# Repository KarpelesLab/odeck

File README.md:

# odeck

An open-hardware USB-C deck you can order fully assembled from JLCPCB and use as a bare PCB the day it
arrives: USB-C upstream, display out, USB-A, SD + microSD, 2.5 GbE, up to **140 W** pass-through
charging, a small status LCD instead of a wall of LEDs, and an RP2350 you can reprogram.

The long-term goal is a **40 Gbps USB4** deck. The first board, **odeck-10**, is a 10 Gbps USB-C deck
built only from parts JLC stocks, to prove out everything the USB4 version will reuse: power, PD,
firmware, display, card reader, Ethernet, board shape and silkscreen.

> **Status (2026-10): schematic complete and reviewed, placement done (DRC-clean, unrouted) — not routed,
> not fabricated.** Placement is code: `hardware/odeck-10/layout/*.py` (one script per board region, see
> `docs/floorplan.md`). The LCD panel and the two JAE USB-C receptacles have no 3D model yet, and the
> GPIO header is shown although it ships unpopulated. More views: [top](docs/images/odeck-10-top.png) ·
> [bottom](docs/images/odeck-10-bottom.png).

## odeck-10 at a glance

| | |
|---|---|
| Upstream | USB-C, USB 3.2 Gen 2 (10 Gbps) + DisplayPort Alt Mode (2-lane HBR3, 4K60) |
| Charging the laptop | USB PD 3.1 EPR up to **140 W** (28 V × 5 A), 100 W SPR fallback |
| Power inputs | USB-C PD in (EPR, up to 48 V) · DC barrel 5.5×2.5 mm 9–24 V · or bus-powered from the laptop |
| Display | Downstream USB-C with DP Alt Mode (works with any USB-C→HDMI/DP cable) |
| USB | 2× USB-A 10 Gbps (BC1.2 charging), downstream USB-C 10 Gbps, forced-5 V "dumb charge" mode with auto-off |
| Storage | SD + microSD (Genesys GL3224) |
| Network | 2.5 GbE (Realtek RTL8156BG) |
| Brains | RP2350B — drives a 2.0" 320×240 IPS status LCD, reads every PD contract / link speed / temperature / port current, and updates every other chip's firmware from a single UF2 |
| Hackable | 2 user buttons, unpopulated GPIO header (series-R + ESD protected), Qwiic connector, SWD |
| Board | 6-layer JLC impedance stack-up (JLC061611-1080A), 130×89 mm, ~800 parts (double-sided), all JLC stock |

### Architecture

```
 Laptop USB-C ══ TUSB1064 ══ USB 10G ══► Microchip USB7206C hub ──► USB-A ×2 · GL3224 (SD/µSD) · RTL8156BG (2.5GbE)
 (10G + DP alt,      ║                                        └──► downstream USB-C ◄══ TUSB1046 ◄═ DP 2-lane
  140 W EPR out)     ╚═════════════ DP lanes + AUX ═══════════════════════════════╝      (USB2 port → RP2350)

 Infineon PMG1-S3: laptop port (EPR source, DP UFP_D) + downstream port (5 V/3 A, DP DFP_D)
 TI TPS26750: USB-C PD-in sink (up to 48 V)        Barrel 9–24 V ─┐
 PD-in ─► ideal-diode OR ◄──────────────────────────────────────────┘ → VIN 9–48 V
   VIN ─► LM51770 buck-boost → 5–28 V × 5 A → laptop (gated, interlocked, hardware OVP)
   VIN ─► LM5148 → 5 V / 8 A → 3.3 V, 1.15 V …     laptop VBUS ─► 5 V when bus-powered
 RP2350B: LCD, buttons, I²C to PD controllers / INA2xx power monitors / 8× TMP1075 / hub SMBus
```

## Repository layout

| Path | What |
|---|---|
| `docs/requirements.md` | Goals and constraints for the whole project (USB4 end goal) |
| `docs/odeck-10.md` | **Start here** — odeck-10 architecture, part choices, design rules, integration items, status |
| `docs/power-budget.md`, `docs/board-layout.md` | Power/thermal budget, outline & placement plan, stack-up |
| `docs/design/*.md` | Per-sheet design notes with every calculation |
| `docs/review/*.md` | Independent schematic and footprint reviews, with resolutions |
| `docs/research/*.md` | Chip, JLC capability and sourcing research (incl. why 40G is not buildable from JLC stock yet) |
| `hardware/odeck-10/` | KiCad 10 project. Schematic sheets are **generated** from `sheets/*.py` |
| `hardware/lib/` | Project symbols, footprints (all checked against manufacturer drawings) and 3D models |
| `tools/schgen/` | Schematics-as-code generator + netlist verification |
| `tools/pcbsync.py` | Scripted "update PCB from schematic" (keeps placed parts where they are; `--refresh` reloads footprints) |
| `tools/apply_layout.py`, `tools/apply_routing.py` | Placement-as-code and routing-as-code runners (`layout/*.py`, `routing/*.py`) |
| `tools/autoroute.py` | Freerouting wrapper for the non-critical nets |
| `tools/bom_check.py` | Checks every part against live JLC stock (rule: JLC parts only, ≥ 5 in stock) |
| `tools/import_lcsc.sh` | Imports LCSC parts (symbol/footprint/3D) via easyeda2kicad |

## Working on it

Requires KiCad 10 (`/Applications/KiCad` on macOS) and Python 3.10+.

```sh
# regenerate every schematic sheet from its Python source and verify the netlist
python3 hardware/odeck-10/sheets/build_all.py

# electrical rules check
/Applications/KiCad/KiCad.app/Contents/MacOS/kicad-cli sch erc hardware/odeck-10/odeck-10.kicad_sch

# every part in JLC stock?  (+ cost summary)
python3 tools/bom_check.py

# push schematic changes into the PCB (uses KiCad's bundled Python)
/Applications/KiCad/KiCad.app/Contents/Frameworks/Python.framework/Versions/3.9/bin/python3 tools/pcbsync.py hardware/odeck-10

# render
/Applications/KiCad/KiCad.app/Contents/MacOS/kicad-cli pcb render --side top -o top.png hardware/odeck-10/odeck-10.kicad_pcb
```

Edit schematics by editing `hardware/odeck-10/sheets/<sheet>.py`, never the generated `.kicad_sch`.
Inter-sheet nets are declared in `tools/schgen/nets.py`.

## Roadmap

1. **odeck-10** (10 Gbps, JLC parts only) — schematic ✅ · review ✅ · footprints ✅ · placement ✅ ·
   routing ⏳ · firmware · order prototypes · bring-up
2. **20/40 Gbps USB4** — waiting on a USB4 hub controller (and its firmware) that can actually be sourced;
   see `docs/research/usb4-hub.md`.

## License

- **Hardware** — everything under `hardware/` (schematics, sheet sources, PCB, symbols, footprints, 3D
  models we created) and the hardware documentation in `docs/`: **CERN-OHL-P v2**
  ([LICENSE-HARDWARE](LICENSE-HARDWARE)).
  Copyright © 2026 Karpelès Lab Inc.
- **Software** — `tools/` and future firmware: **MIT** ([LICENSE-SOFTWARE](LICENSE-SOFTWARE)).

Not covered: third-party datasheets in `docs/datasheets/` (copyright of their manufacturers, included for
reference), footprints/3D models derived from KiCad's libraries or LCSC/EasyEDA (their own terms), and vendor
firmware/libraries (e.g. Infineon's PD stack), which are fetched at build time and never committed.

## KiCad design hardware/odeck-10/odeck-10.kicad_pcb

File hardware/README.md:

# Hardware

KiCad 10 projects.

- `odeck-10/` — 10 Gbps prototype (see `../docs/odeck-10.md`, `../docs/board-layout.md`)
  - Hierarchical schematic: one sheet per block (power input, laptop power out, rails, PD controller,
    USB-C muxes & DP, USB hub, USB-A, Ethernet, card reader, MCU, display & UI, sensors)
  - PCB: JLC061611-1080A 6-layer stackup, 110 × 75 mm provisional outline, JLC design rules, net classes
- `lib/` — shared project symbol/footprint libraries (`odeck.kicad_sym`, `odeck.pretty`), referenced via
  each project's `sym-lib-table` / `fp-lib-table`. Parts from LCSC can be imported with `easyeda2kicad`.

CLI checks:

```sh
K=/Applications/KiCad/KiCad.app/Contents/MacOS/kicad-cli
$K sch erc odeck-10/odeck-10.kicad_sch
$K pcb drc odeck-10/odeck-10.kicad_pcb
```

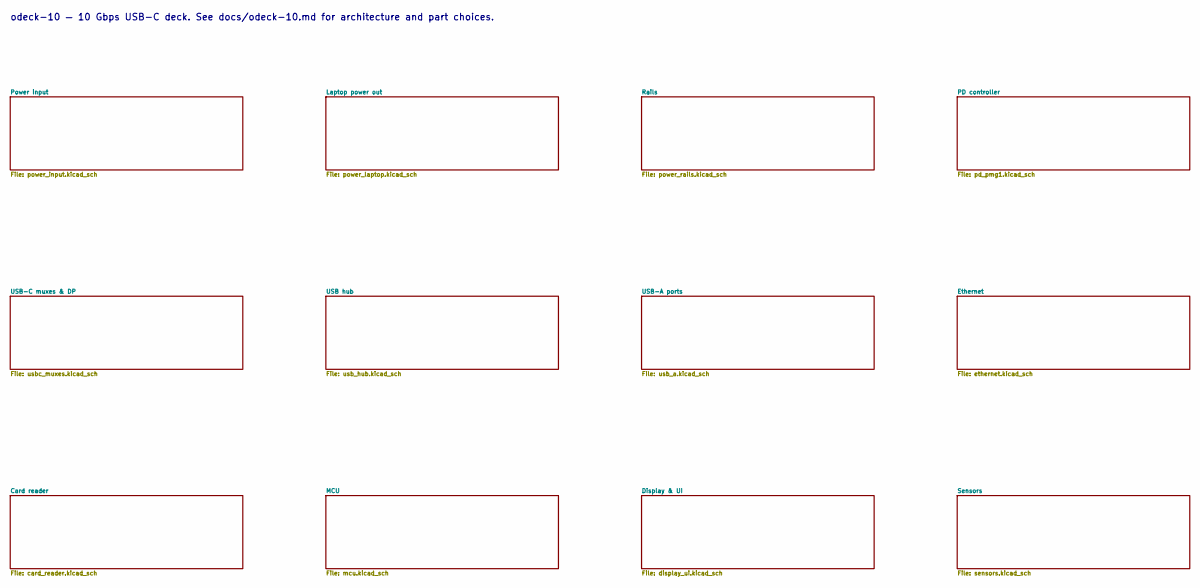
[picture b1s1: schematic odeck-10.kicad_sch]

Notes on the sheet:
odeck-10 — 10 Gbps USB-C deck. See docs/odeck-10.md for architecture and part choices.

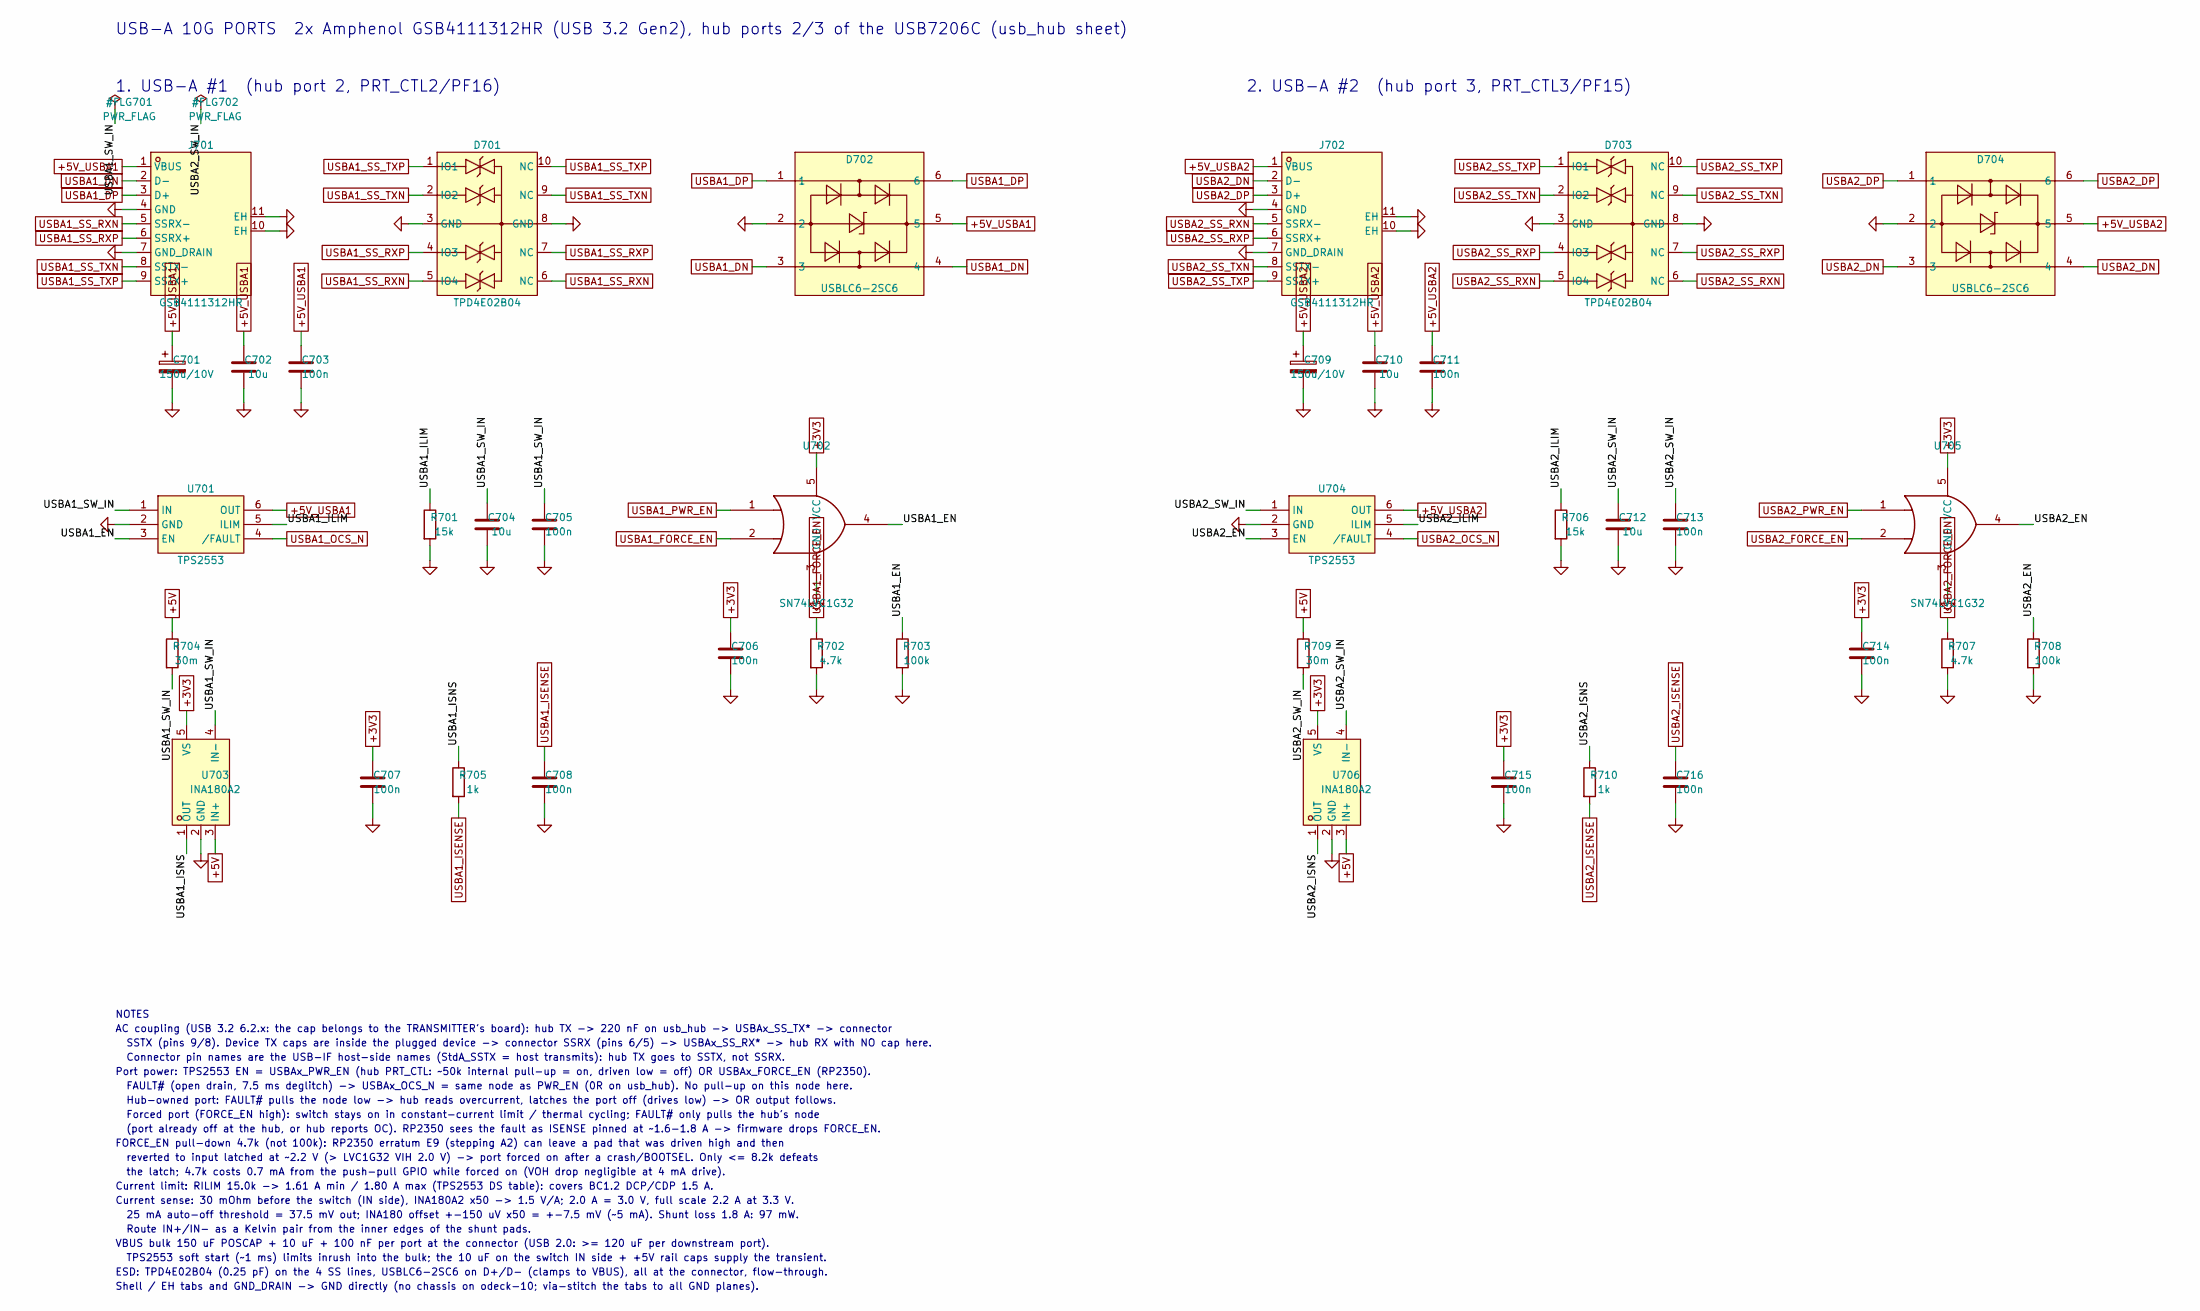
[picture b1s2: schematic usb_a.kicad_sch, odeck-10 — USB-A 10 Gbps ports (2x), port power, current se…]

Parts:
C701, C709: 150u/10V; CP_EIA-7343-31_Kemet-D; LCSC C347559
C702, C704, C710, C712: 10u; C_0805_2012Metric; LCSC C15850
C703, C705, C706, C707, C708, C711, C713, C714, C715, C716: 100n; C_0402_1005Metric; LCSC C1525
D701, D703: TPD4E02B04; USON-10_L2.5-W1.0-P0.50-BL; MPN TPD4E02B04DQAR; LCSC C106794
D702, D704: USBLC6-2SC6; SOT-23-6_L2.9-W1.6-P0.95-LS2.8-BL; MPN USBLC6-2SC6; LCSC C7519
J701, J702: GSB4111312HR; USB-A_Amphenol_GSB4111312HR; MPN GSB4111312HR; LCSC C5429382
R701, R706: 15k; R_0402_1005Metric; LCSC C25756
R702, R707: 4.7k; R_0402_1005Metric; LCSC C25900
R703, R708: 100k; R_0402_1005Metric; LCSC C25741
R704, R709: 30m; R_0805_2012Metric; LCSC C858599
R705, R710: 1k; R_0402_1005Metric; LCSC C11702
U701, U704: TPS2553; SOT-23-6_L2.9-W1.6-P0.95-LS2.8-BR; MPN TPS2553DBVR; LCSC C55266
U702, U705: SN74LVC1G32; SOT-23-5; LCSC C10096
U703, U706: INA180A2; SOT-23-5_L3.0-W1.7-P0.95-LS2.8-BL; MPN INA180A2IDBVR; LCSC C192764

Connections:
+3V3: C706.1, C707.1, C714.1, C715.1, U702.5 (VCC), U703.5 (VS), U705.5 (VCC), U706.5 (VS); also elsewhere on the board
+5V: R704.1, R709.1, U703.3 (IN+), U706.3 (IN+); also elsewhere on the board
+5V_USBA1: C701.1, C702.1, C703.1, D702.5, J701.1 (VBUS), U701.6 (OUT)
+5V_USBA2: C709.1, C710.1, C711.1, D704.5, J702.1 (VBUS), U704.6 (OUT)
/USB-A ports/USBA1_EN: R703.1, U701.3 (EN), U702.4
/USB-A ports/USBA1_ILIM: R701.1, U701.5 (ILIM)
/USB-A ports/USBA1_ISNS: R705.1, U703.1 (OUT)
/USB-A ports/USBA1_SW_IN: C704.1, C705.1, R704.2, U701.1 (IN), U703.4 (IN-)
/USB-A ports/USBA2_EN: R708.1, U704.3 (EN), U705.4
/USB-A ports/USBA2_ILIM: R706.1, U704.5 (ILIM)
/USB-A ports/USBA2_ISNS: R710.1, U706.1 (OUT)
/USB-A ports/USBA2_SW_IN: C712.1, C713.1, R709.2, U704.1 (IN), U706.4 (IN-)
GND: C701.2, C702.2, C703.2, C704.2, C705.2, C706.2, C707.2, C708.2, C709.2, C710.2, C711.2, C712.2, C713.2, C714.2, C715.2, C716.2, D701.3 (GND), D701.8 (GND), D702.2, D703.3 (GND), D703.8 (GND), D704.2, J701.4 (GND), J701.7 (GND_DRAIN), J701.10 (EH), J701.11 (EH), J702.4 (GND), J702.7 (GND_DRAIN), J702.10 (EH), J702.11 (EH), R701.2, R702.2, R703.2, R706.2, R707.2, R708.2, U701.2 (GND), U702.3 (GND), U703.2 (GND), U704.2 (GND), U705.3 (GND), U706.2 (GND); also elsewhere on the board
USBA1_DN: D702.3, D702.4, J701.2 (D-); also elsewhere on the board
USBA1_DP: D702.1, D702.6, J701.3 (D+); also elsewhere on the board
USBA1_FORCE_EN: R702.1, U702.2; also elsewhere on the board
USBA1_ISENSE: C708.1, R705.2; also elsewhere on the board
USBA1_OCS_N: U701.4 (/FAULT); also elsewhere on the board
USBA1_PWR_EN: U702.1; also elsewhere on the board
USBA1_SS_RXN: D701.5 (IO4), D701.6 (NC), J701.5 (SSRX-); also elsewhere on the board
USBA1_SS_RXP: D701.4 (IO3), D701.7 (NC), J701.6 (SSRX+); also elsewhere on the board
USBA1_SS_TXN: D701.2 (IO2), D701.9 (NC), J701.8 (SSTX-); also elsewhere on the board
USBA1_SS_TXP: D701.1 (IO1), D701.10 (NC), J701.9 (SSTX+); also elsewhere on the board
USBA2_DN: D704.3, D704.4, J702.2 (D-); also elsewhere on the board
USBA2_DP: D704.1, D704.6, J702.3 (D+); also elsewhere on the board
USBA2_FORCE_EN: R707.1, U705.2; also elsewhere on the board
USBA2_ISENSE: C716.1, R710.2; also elsewhere on the board
USBA2_OCS_N: U704.4 (/FAULT); also elsewhere on the board
USBA2_PWR_EN: U705.1; also elsewhere on the board
USBA2_SS_RXN: D703.5 (IO4), D703.6 (NC), J702.5 (SSRX-); also elsewhere on the board
USBA2_SS_RXP: D703.4 (IO3), D703.7 (NC), J702.6 (SSRX+); also elsewhere on the board
USBA2_SS_TXN: D703.2 (IO2), D703.9 (NC), J702.8 (SSTX-); also elsewhere on the board
USBA2_SS_TXP: D703.1 (IO1), D703.10 (NC), J702.9 (SSTX+); also elsewhere on the board

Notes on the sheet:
USB-A 10G PORTS 2x Amphenol GSB4111312HR (USB 3.2 Gen2), hub ports 2/3 of the USB7206C (usb_hub sheet)
1. USB-A #1 (hub port 2, PRT_CTL2/PF16)
2. USB-A #2 (hub port 3, PRT_CTL3/PF15)
NOTES
AC coupling (USB 3.2 6.2.x: the cap belongs to the TRANSMITTER's board): hub TX -> 220 nF on usb_hub -> USBAx_SS_TX* -> connector
SSTX (pins 9/8). Device TX caps are inside the plugged device -> connector SSRX (pins 6/5) -> USBAx_SS_RX* -> hub RX with NO cap here.
Connector pin names are the USB-IF host-side names (StdA_SSTX = host transmits): hub TX goes to SSTX, not SSRX.
Port power: TPS2553 EN = USBAx_PWR_EN (hub PRT_CTL: ~50k internal pull-up = on, driven low = off) OR USBAx_FORCE_EN (RP2350).
FAULT# (open drain, 7.5 ms deglitch) -> USBAx_OCS_N = same node as PWR_EN (0R on usb_hub). No pull-up on this node here.
Hub-owned port: FAULT# pulls the node low -> hub reads overcurrent, latches the port off (drives low) -> OR output follows.
Forced port (FORCE_EN high): switch stays on in constant-current limit / thermal cycling; FAULT# only pulls the hub's node
(port already off at the hub, or hub reports OC). RP2350 sees the fault as ISENSE pinned at ~1.6-1.8 A -> firmware drops FORCE_EN.
FORCE_EN pull-down 4.7k (not 100k): RP2350 erratum E9 (stepping A2) can leave a pad that was driven high and then
reverted to input latched at ~2.2 V (> LVC1G32 VIH 2.0 V) -> port forced on after a crash/BOOTSEL. Only <= 8.2k defeats
the latch; 4.7k costs 0.7 mA from the push-pull GPIO while forced on (VOH drop negligible at 4 mA drive).
Current limit: RILIM 15.0k -> 1.61 A min / 1.80 A max (TPS2553 DS table): covers BC1.2 DCP/CDP 1.5 A.
Current sense: 30 mOhm before the switch (IN side), INA180A2 x50 -> 1.5 V/A; 2.0 A = 3.0 V, full scale 2.2 A at 3.3 V.
25 mA auto-off threshold = 37.5 mV out; INA180 offset +-150 uV x50 = +-7.5 mV (~5 mA). Shunt loss 1.8 A: 97 mW.
Route IN+/IN- as a Kelvin pair from the inner edges of the shunt pads.
VBUS bulk 150 uF POSCAP + 10 uF + 100 nF per port at the connector (USB 2.0: >= 120 uF per downstream port).
TPS2553 soft start (~1 ms) limits inrush into the bulk; the 10 uF on the switch IN side + +5V rail caps supply the transient.
ESD: TPD4E02B04 (0.25 pF) on the 4 SS lines, USBLC6-2SC6 on D+/D- (clamps to VBUS), all at the connector, flow-through.
Shell / EH tabs and GND_DRAIN -> GND directly (no chassis on odeck-10; via-stitch the tabs to all GND planes).

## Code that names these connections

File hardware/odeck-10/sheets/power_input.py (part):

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           "EPR_BLK_G unused (no 5 V source FET: sink-only port). SBU channels unused.",
           at=(20.32, 12.7))
    s.part("odeck:DX07S024XJ1R1100", "J", "USB-C PD-in", at=(45.72, 76.2),
           pins={"VBUS": "VBUS_PDIN", "CC1": "PDIN_C_CC1", "CC2": "PDIN_C_CC2", "GND": "GND", "0": "GND"},
           nc=["A2", "A3", "B2", "B3", "A10", "A11", "B10", "B11", "A6", "A7", "B6", "B7", "A8", "B8"],
           desc="USB-C receptacle 24P, 5 A / 48 V, PD-in (power only)")
    s.part("odeck:SMCJ51A_C408371", "D", TVS_PDIN[1], at=(91.44, 60.96), pins={"C": "VBUS_PDIN", "A": "GND"},
           lcsc=TVS_PDIN[0], mpn=TVS_PDIN[1], desc="TVS 51 V uni 5 kW (SMC), VBUS_PDIN")
    s.c("2.2u/100V", "VBUS_PDIN", "GND", size="1210", at=(83.82, 81.28), lcsc=C_2U2_100V)
    s.c("100n/100V", "VBUS_PDIN", "GND", size="0805", at=(93.98, 81.28), lcsc=C_100N_100V)
    s.flag("VBUS_PDIN", at=(104.14, 81.28))

    s.part("odeck:TPD4S480RUKR_C43131250", "U", "TPD4S480", at=(152.4, 76.2),
           pins={"VBUS": "VBUS_PDIN", "VBUS_LV": "PDIN_VBUS_LV", "EPR_EN": "PDIN_EPR_EN", "VPWR": "PD_LDO_3V3",
                 "VBIAS": "PDIN_VBIAS", "C_CC1": "PDIN_C_CC1", "RPD_G1": "PDIN_C_CC1", "C_CC2": "PDIN_C_CC2",
                 "RPD_G2": "PDIN_C_CC2", "CC1": "PDIN_CC1", "CC2": "PDIN_CC2", "~{FLT}": "PDIN_FLT_N",
                 "GND": "GND", "EP": "GND"},
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           "  (SafeMode alternative: ADCIN1 -> LDO_3V3, ADCIN2 -> GND = 7/0, address 0x20.)\n"
           "Config/patch from AT24C512C (64 KB >= 36 KB req.) at 0x50 on the private I2Cc bus.\n"
           "  RP2350 updates it through the TPS26750 host interface (I2Ct, 0x21); I2Cc test pads for recovery.\n"
           "GPIO0 = EPR_EN (to TPD4S480), GPIO1 = PDIN_PRESENT (informational only, 47k series: <= 60 uA into an\n"
           "  unpowered PMG1/RP2350 pin; config: high while sink contract active),\n"
           "GPIO2 = TPD4S480 FLT# input, other GPIOs strapped to GND through 100k (datasheet: tie low if unused).\n"
           "PP5V tied to GND: sink-only port, no 5 V sourcing / VCONN (verify with TI).\n"
           "I2C_PD pull-ups live on the MCU sheet; PDIN_INT_N pull-up here.",
           at=(205.74, 12.7))
    s.part("odeck:TPS26750SRSMR_C42166327", "U", "TPS26750", at=(271.78, 83.82),
           pins={"VIN_3V3": "+3V3", "LDO_3V3": "PD_LDO_3V3", "LDO_1V5": "PD_LDO_1V5",
                 "VBUS": "PDIN_VBUS_LV", "PP5V": "GND", "CC1": "PDIN_CC1", "CC2": "PDIN_CC2",
                 "ADCIN1": "PD_ADCIN1", "ADCIN2": "PD_ADCIN2",
                 "GPIO0": "PDIN_EPR_EN", "GPIO1": "PDIN_PRES_L", "GPIO2": "PDIN_FLT_N",
                 "GPIO3": "PD_GPIO3", "GPIO4/USB_P/LD1": "PD_GPIO4", "GPIO5/USB_N/LD2": "PD_GPIO5",
                 "GPIO6": "PD_GPIO6", "GPIO7": "PD_GPIO7", "GPIO11": "PD_GPIO11",
                 "I2Ct_SDA": "I2C_PD_SDA", "I2Ct_SCL": "I2C_PD_SCL", "~{I2Ct_IRQ}": "PDIN_INT_N",
                 "I2Cc_SDA": "PD_I2CC_SDA", "I2Cc_SCL": "PD_I2CC_SCL", "~{I2Cc_IRQ}": "PD_I2CC_IRQ_N",
                 "POWER_PATH_EN": "PD_PP_EN_HV", "GND": "GND"},
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    s.r("4.7k", "PD_I2CC_SCL", "PD_LDO_3V3", at=(x0 + 121.92, y0), lcsc=R_4K7)   # during dead-battery EEPROM boot
    # unused GPIOs -> GND through 100k (Hi-Z by default; resistor protects if a config drives them)
    y1 = 180.34
    for i, g in enumerate(["PD_GPIO3", "PD_GPIO4", "PD_GPIO5", "PD_GPIO6", "PD_GPIO7", "PD_GPIO11"]):
        s.r("100k", g, "GND", at=(x0 + i * 10.16, y1), lcsc=R_100K)
    # PDIN_PRESENT: GPIO1, default low. 47k series: GPIO1 can be high (VBUS-LDO powered) while PMG1 P7.2 (not
    # fail-safe) and the RP2350 are unpowered -> (3.3 - 0.5) V / 47k = 60 uA < 0.5 mA PMG1 injection limit.
    s.r("100k", "PDIN_PRES_L", "GND", at=(x0 + 60.96, y1), lcsc=R_100K)
    s.r("47k", "PDIN_PRES_L", "PDIN_PRESENT", at=(x0 + 71.12, y1), lcsc=R_47K)
    s.r("100k", "PDIN_EPR_EN", "GND", at=(x0 + 81.28, y1), lcsc=R_100K)

    s.part("odeck:AT24C512C-SSHD-T", "U", "AT24C512C", at=(355.6, 76.2),
           pins={"A0": "GND", "A1": "GND", "A2": "GND", "WP": "GND", "VCC": "PD_LDO_3V3", "GND": "GND",
                 "SDA": "PD_I2CC_SDA", "SCL": "PD_I2CC_SCL"},
           desc="512 Kbit I2C EEPROM, TPS26750 config/patch (0x50)")
    s.c("100n", "PD_LDO_3V3", "GND", at=(345.44, 96.52), lcsc=C_100N_16V)
    s.part("Connector:TestPoint", "TP", "I2Cc_SDA", "TestPoint:TestPoint_Pad_D1.0mm", at=(360.68, 96.52),
           pins={"1": "PD_I2CC_SDA"})
    s.part("Connector:TestPoint", "TP", "I2Cc_SCL", "TestPoint:TestPoint_Pad_D1.0mm", at=(370.84, 96.52),
           pins={"1": "PD_I2CC_SCL"})

    # POWER_PATH_EN buffer (datasheet Fig. 8-5): POWER_PATH_EN is a 6-12 V / 10 uA charge-pump output,
    # buffered by two NFETs into a logic-level PD_SINK_EN (LDO_3V3 domain).
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           "Q103: pulls PD_OK low while the sink path is off.", at=(480.06, 154.94))
    xb, yb = 495.3, 180.34
    s.part("Transistor_FET:2N7002", "Q", "2N7002", at=(xb, yb), lcsc="C8545",
           pins={"G": "PD_PP_EN_HV", "D": "PD_PP_EN_INV", "S": "GND"})
    s.part("Transistor_FET:2N7002", "Q", "2N7002", at=(xb + 22.86, yb), lcsc="C8545",
           pins={"G": "PD_PP_EN_INV", "D": "PD_SINK_EN", "S": "GND"})
    s.part("Transistor_FET:2N7002", "Q", "2N7002", at=(xb + 45.72, yb), lcsc="C8545",
           pins={"G": "PD_PP_EN_INV", "D": "PD_OK", "S": "GND"})
    s.r("100k", "PD_PP_EN_INV", "PD_LDO_3V3", at=(xb, yb + 25.4), lcsc=R_100K)
    s.r("100k", "PD_SINK_EN", "PD_LDO_3V3", at=(xb + 22.86, yb + 25.4), lcsc=R_100K)

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           "Reverse/backfeed from VIN (barrel or buck-boost) blocked by Q104 (ideal diode).\n"
           "Conduction: 5 A x 2 x 2.6 mOhm = 0.13 W.",
           at=(406.4, 12.7))
    s.part(FET, "Q", "BSC026N08NS5", at=(429.26, 63.5), pins={"S": "VBUS_PDIN", "D": "PD_MID", "G": "PD_DGATE"},
           desc="80 V NFET, PD-in ideal diode")
    s.part(FET, "Q", "BSC026N08NS5", at=(487.68, 63.5), pins={"S": "VIN_OR", "D": "PD_MID", "G": "PD_HGATE"},
           desc="80 V NFET, PD-in load switch")
    s.part("odeck:LM74800QDRRRQ1", "U", "LM74800-Q1", at=(457.2, 101.6),
           pins={"DGATE": "PD_DGATE", "A": "VBUS_PDIN", "VSNS": "VBUS_PDIN", "SW": "PD_OV_TOP", "OV": "PD_OV",
                 "EN/UVLO": "PD_SINK_EN", "GND": "GND", "HGATE": "PD_HGATE", "OUT": "VIN_OR", "VS": "PD_MID",
                 "CAP": "PD_CAP", "C": "PD_MID"},
           nc=["RTN"], desc="Ideal diode + load switch controller, PD-in")
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           "Inrush: HGATE 55 uA into 47 nF -> 1.17 V/ms. Conduction: 8.3 A x 2 x 2.6 mOhm = 0.36 W.",
           at=(20.32, 198.12))
    s.part("odeck:PJ-063BH_C3095900", "J", "PJ-063BH", at=(30.48, 254.0),
           pins={"1": "VBAR", "2": "GND"}, nc=["0"], desc="DC jack 5.5x2.5 mm, 8 A")
    s.part("odeck:SMCJ48CA_C408370", "D", TVS_BAR[1], at=(63.5, 246.38), pins={"1": "VBAR", "2": "GND"},
           lcsc=TVS_BAR[0], mpn=TVS_BAR[1], desc="TVS 48 V bidirectional 5 kW (SMC), barrel")
    s.c("100n/100V", "VBAR", "GND", size="0805", at=(78.74, 261.62), lcsc=C_100N_100V)
    s.part(FET, "Q", "BSC026N08NS5", at=(116.84, 246.38), pins={"S": "VBAR", "D": "BAR_MID", "G": "BAR_DGATE"},
           desc="80 V NFET, barrel ideal diode")
    s.part(FET, "Q", "BSC026N08NS5", at=(175.26, 246.38), pins={"S": "VIN_OR", "D": "BAR_MID", "G": "BAR_HGATE"},
           desc="80 V NFET, barrel OV/UVLO/enable switch")
    s.part("odeck:LM74800QDRRRQ1", "U", "LM74800-Q1", at=(147.32, 284.48),
           pins={"DGATE": "BAR_DGATE", "A": "VBAR", "VSNS": "VBAR", "SW": "BAR_SW", "OV": "BAR_OV",
                 "EN/UVLO": "BAR_EN", "GND": "GND", "HGATE": "BAR_HGATE", "OUT": "VIN_OR", "VS": "BAR_MID",
                 "CAP": "BAR_CAP", "C": "BAR_MID"},
           nc=["RTN"], desc="Ideal diode + load switch controller, barrel (RTN pad floating per datasheet)")
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           "PD_OK: TLV6700 window on VBUS_PDIN, 1M/47k/7.5k: UV 7.7 V, OV 56.2 V, AND sink path on (Q103).\n"
           "  A 5 V-only PD contract therefore does NOT count as external power.\n"
           "The laptop sink switch is released only when EXT_PWR_PRESENT AND PG_5V (power_laptop), so a\n"
           "  slightly early EXT_PWR_PRESENT (VIN still ramping) never browns out the deck.\n"
           "Open-drain outputs wired-AND per source, pull-ups to +3V3; 74LVC1G32 OR -> EXT_PWR_PRESENT.\n"
           "All of it runs from +3V3, which exists whenever anything powers the deck.",
           at=(287.02, 198.12))
    x4, y4 = 304.8, 248.92
    s.part("odeck:TLV6700DDCR", "U", "TLV6700", at=(x4 + 15.24, y4),
           pins={"VDD": "+3V3", "GND": "GND", "INA+": "BAR_MON_UV", "INB-": "BAR_MON_OV",
                 "OUTA": "BAR_OK", "OUTB": "BAR_OK"}, desc="Window comparator, barrel present")
    s.part("Device:D", "D", "1N4148W", "Diode_SMD:D_SOD-123", at=(x4 - 30.48, y4 + 27.94), lcsc="C81598",
           pins={"A": "VBAR", "K": "BAR_MON_TOP"})
    s.r("1M", "BAR_MON_TOP", "BAR_MON_UV", size="0805", at=(x4, y4 + 27.94), lcsc=R_1M_0805)
    s.r("39k", "BAR_MON_UV", "BAR_MON_OV", size="0603", at=(x4 + 10.16, y4 + 27.94), lcsc=R_39K)
    s.r("15k", "BAR_MON_OV", "GND", at=(x4 + 20.32, y4 + 27.94), lcsc=R_15K)
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
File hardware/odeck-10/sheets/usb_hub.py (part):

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        "XTALI/CLK_IN": "HUB_XI", "XTALO": "HUB_XO",
        "TESTEN": "GND", "TEST1": "HUB_TEST1", "TEST2": "HUB_TEST2", "TEST3": "HUB_TEST3",
        "~{CFG_STRAP1}": "HUB_CFG1", "~{CFG_STRAP2}": "HUB_CFG2", "~{CFG_STRAP3}": "HUB_CFG3",
        "PF30/VBUS_MON_UP": "HUB_VBUS_DET",
        # SMBus slave (Configuration 3: PF26 = SLV_I2C_CLK, PF27 = SLV_I2C_DATA)
        "PF26": "HUB_SMB_CLK", "PF27": "HUB_SMB_DAT",
        # port power / overcurrent (combined PRT_CTLx pins): USB-A #1 = port 2, USB-A #2 = port 3
        "PF16": "USBA1_PWR_EN", "PF15": "USBA2_PWR_EN",
        # SPI (optional flash, DNP) / straps
        "SPI_CE_N/~{CFG_NON_REM}/PF20": "HUB_SPI_CE_N",
        "SPI_D0/~{CFG_BC_EN}/PF22": "HUB_SPI_D0",
        "SPI_CLK/PF21": "HUB_SPI_CLK", "SPI_D1/PF23": "HUB_SPI_D1",
        "SPI_D2/PF24": "HUB_SPI_D2", "SPI_D3/PF25": "HUB_SPI_D3",
        # unused programmable functions with "weak pull-down" termination (DS table 3-6)
        "PF3": "HUB_PF3", "PF4": "HUB_PF4", "PF5": "HUB_PF5", "PF6": "HUB_PF6", "PF7": "HUB_PF7",
        "PF18": "HUB_PF18", "PF19": "HUB_PF19", "PF31": "HUB_PF31", "PF29": "HUB_PF29",
    }
    for n, (pre, (dp, dm, txp, txm, rxp, rxm)) in PORTS.items():
        pins.update({str(dp): f"{pre}_DP", str(dm): f"{pre}_DN",
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    _note(s, "4. CLOCK / BIAS / TEST / STRAPS", (x0, y0), 2.0)
    y = y0 + 20.32
    s.part("Device:Crystal_GND24", "Y", "25MHz", "Crystal:Crystal_SMD_3225-4Pin_3.2x2.5mm", at=(x0 + 10.16, y),
           pins={"1": "HUB_XI", "3": "HUB_XO", "2": "GND", "4": "GND"}, lcsc=XTAL_25M,
           desc="25 MHz crystal CL 12 pF, +-10 ppm tol / +-20 ppm stab. (hub needs +-50 ppm)")
    s.c("20p", "HUB_XI", "GND", at=(x0 + 30.48, y), lcsc=C_20P, desc="CL = (20+2)/2 = 11 pF with ~2 pF stray")
    s.c("20p", "HUB_XO", "GND", at=(x0 + 40.64, y), lcsc=C_20P)
    s.r("12k", "HUB_RBIAS", "GND", at=(x0 + 50.8, y), lcsc=R_12K, desc="RBIAS 12.0k 1 %, at pin 100, short GND return")
    s.r("10k", "HUB_TEST1", "+3V3", at=(x0 + 60.96, y), lcsc=R_10K, desc="TEST1 pull-up (mandatory)")
    s.r("10k", "HUB_TEST2", "+3V3", at=(x0 + 71.12, y), lcsc=R_10K, desc="TEST2 pull-up (mandatory)")
    s.r("10k", "HUB_TEST3", "+3V3", at=(x0 + 81.28, y), lcsc=R_10K, desc="TEST3 pull-up (mandatory)")
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    s.r("10k", "HUB_SPI_D3", "+3V3", at=(x0 + 91.44, y), lcsc=R_10K, dnp=True,
        desc="SPI_D3 = flash HOLD#: fit with U602 (and remove the PD)")
    y = y0 + 60.96
    for i, pf in enumerate(["PF3", "PF4", "PF5", "PF6", "PF7", "PF18", "PF19", "PF31", "PF29"]):
        s.r("100k", f"HUB_{pf}", "GND", at=(x0 + i * 10.16, y), lcsc=R_100K, desc=f"{pf} unused: weak PD (DS table 3-6)")
    _note(s, "Straps are latched at POR / RESET_N rising edge (hold >= 1 ms after). Config 3 (STRAP2 200k PD, STRAP1 10k PD) is the\n"
             "only valid USB7206C mode: PF26/27 = SMBus slave, PF15/16 = PRT_CTL3/2, PF30 = VBUS_DET, PF18/31 = I2C master (unused).\n"
             "PF3-7 (I2S), PF18/31 (I2C master), PF19 (MIC_DET), PF29 (GPIO93): unused -> 100k PD.  PF8/9 NC.  PRT_CTL1/4/5/6 float.\n"
             "CFG_NON_REM 200k PU = port 1 non-removable; CFG_BC_EN 10k PU = BC1.2 on ports 1-3. RP2350 refines both over SMBus\n"
             "(non-removable 1/4/6, BC on 2/3 only) when it is alive; with the RP2350 dead the strap defaults are safe.",
          (x0, y0 + 71.12))
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    s.r("10k", "HUB_RESET_N", "+3V3", at=(x0, y), lcsc=R_10K, desc="RESET_N pull-up (all drivers open-drain)")
    s.c("1n", "HUB_RESET_N", "GND", at=(x0 + 10.16, y), lcsc=C_1N, desc="RESET_N filter (Microchip checklist)")
    s.part("Device:D_Schottky", "D", "BAT54WS", "Diode_SMD:D_SOD-323", at=(x0 + 22.86, y),
           pins={"A": "HUB_RESET_N", "K": "RAILS_PG"}, lcsc=D_SCHOTTKY,
           desc="Wire-OR: RAILS_PG low (+1V15 not good) holds RESET_N low; RP2350 pulling RESET_N does not load RAILS_PG")
    s.r("47k", "VBUS_LAPTOP", "HUB_VBUS_SNS", size="0402", at=(x0 + 38.1, y), lcsc=R_47K,
        desc="VBUS sense divider top (laptop VBUS 4.4-28 V)")
    s.r("68k", "HUB_VBUS_SNS", "GND", size="0603", at=(x0 + 48.26, y), lcsc=R_68K, desc="VBUS sense divider bottom: 4.4 V -> 2.60 V")
    s.part("Device:D_Schottky", "D", "BAT54WS", "Diode_SMD:D_SOD-323", at=(x0 + 60.96, y),
           pins={"A": "HUB_VBUS_SNS", "K": "+3V3"}, lcsc=D_SCHOTTKY,
           desc="Clamps the sense node to ~3.6 V when laptop VBUS is 9-28 V (<0.5 mA into +3V3 at 28 V)")
    s.r("10k", "HUB_SMB_CLK", "HUB_SMB_PU", at=(x0 + 76.2, y), lcsc=R_10K,
        desc="SMBus pull-up powered by RP2350 GPIO (10k: hub detects these at boot)")
    s.r("10k", "HUB_SMB_DAT", "HUB_SMB_PU", at=(x0 + 86.36, y), lcsc=R_10K, desc="SMBus pull-up powered by RP2350 GPIO")
    s.r("4.7k", "HUB_SMB_PU", "GND", at=(x0 + 96.52, y), lcsc=R_4K7,
        desc="Keeps pull-up rail at 0 V when RP2350 is off/BOOTSEL -> hub boots stand-alone (4.7k: RP2350-E9)")
    _note(s, "RESET_N = HUB_RESET_N (RP2350 open-drain) AND RAILS_PG (TPS62933P PG, open drain, 100k on power_rails) via D601.\n"
             "  Hub held in standby until +1V15 is in regulation (implies +3V3 up); 10k pull-up then releases it. trst >= 5 us.\n"
             "VBUS_DET (PF30): VBUS_LAPTOP -> 47k/68k (x0.591) + BAT54WS clamp to +3V3 -> HUB_VBUS_SNS -> 74LVC1G17 (+3V3, Schmitt,\n"
             "  5.5 V-tolerant input) -> 15k/49.9k -> PF30.  Sense node: 4.4 V -> 2.60 V (> VT+ max 2.0 V), 28 V -> ~3.6 V clamp (OK for\n"
             "  the LVC input), vSafe0V 0.8 V -> 0.47 V (< VT- min 0.8 V). PF30 high = +3V3 x 0.769 = 2.46-2.64 V for +3V3 3.20-3.43 V\n"
             "  (<= 2.7 V checklist 5.1, > VIH 2.1 V); 11k/49.9k from the checklist would give 2.73 V at our 3.33 V rail -> 15k.\n"
             "  Buffer powered from +3V3 = same rail as VDD33 -> VBUS_DET can never rise before VDD33.\n"
             "  VBUS present = laptop attached (deck sources VBUS only after attach). Limitation (review data #6): VBUS also exists for\n"
             "  a powered-off laptop / charge-only cable -> hub waits as CDP, USB-A get no VBUS until FORCE_EN (firmware).\n"
             "  VBUS_DET = 0 (no laptop): BC1.2 ports run as DCP; VBUS_DET = 1: CDP once the host powers the port.\n"
             "SMBus slave addr 0x2D. Pull-ups only when HUB_SMB_PU (RP2350 GPIO) is high -> hub enters CFG_SMBUS and waits for\n"
             "  the RP2350's config + USB_ATTACH_WITH_SMBUS (AA56h). HUB_SMB_PU low/floating (RP2350 off, BOOTSEL, broken FW):\n"
             "  no pull-ups seen -> hub boots from ROM+straps+OTP immediately -> RP2350 BOOTSEL (UF2) still enumerates on port 6.\n"
             "  Firmware: SMB_PU high -> RESET_N low >= 5 us -> release -> wait >= 40 ms -> config -> AA56h. No other pull-ups on this bus.",
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        desc="Net tie: PRT_CTL2 drives switch EN and senses FAULT# on the same pin")
    s.r("0", "USBA2_PWR_EN", "USBA2_OCS_N", at=(x0 + 10.16, y), lcsc=R_0,
        desc="Net tie: PRT_CTL3 drives switch EN and senses FAULT# on the same pin")
    _note(s, "USB-A #1 = hub port 2 (PRT_CTL2, PF16), USB-A #2 = hub port 3 (PRT_CTL3, PF15). Port on: pin = input + internal ~50k\n"
             "  pull-up (EN high), switch FAULT# (open drain) pulls it low = overcurrent; port off: hub drives it low.\n"
             "  USBAx_PWR_EN and USBAx_OCS_N are therefore the SAME node (0R ties, R630/R631). Do NOT add an external pull-up.\n"
             "  usb_a sheet: TPS2553 EN = PWR_EN OR FORCE_EN (gate input, high-Z), FAULT# open-drain -> OCS_N.\n"
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    x0, y0 = 304.8, 297.18
    _note(s, "7. OPTIONAL SPI FLASH (DNP)  only for Microchip-supplied custom firmware; ROM + straps + SMBus/OTP is the plan", (x0, y0), 2.0)
    s.part("odeck:SST26VF016B-104I_SN", "U", "SST26VF016B", at=(x0 + 30.48, y0 + 17.78),
           pins={"~{CE}": "HUB_SPI_CE_N", "SCK": "HUB_SPI_CLK", "SI/SIO0": "HUB_SPI_D0", "SO/SIO1": "HUB_SPI_D1",
                 "~{WP}/SIO2": "HUB_SPI_D2", "HOLD/SIO3": "HUB_SPI_D3", "VDD": "+3V3", "VSS": "GND"},
           lcsc=FLASH, dnp=True, desc="16 Mbit SQI flash, hub-verified part (USB7206 checklist 9.2). DNP")
    s.c("100n", "+3V3", "GND", at=(x0 + 66.04, y0 + 17.78), lcsc=C_100N, dnp=True, desc="Flash decoupling (DNP)")
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    # VBUS_DET buffer (review data #2) - placed last so earlier references keep their numbers
    y2 = 167.64
    s.part("74xGxx:74LVC1G17", "U", "74LVC1G17", "Package_TO_SOT_SMD:SOT-23-5", at=(419.1, y2),
           pins={"2": "HUB_VBUS_SNS", "4": "HUB_VBUS_BUF", "5": "+3V3", "3": "GND"}, nc=["1"], lcsc=BUF_ST,
           mpn="74LVC1G17W5-7", desc="VBUS_DET Schmitt buffer on +3V3: input 5.5 V tolerant, output <= +3V3")
    s.c("100n", "+3V3", "GND", at=(434.34, y2), lcsc=C_100N, desc="VBUS_DET buffer decoupling")
    s.r("15k", "HUB_VBUS_BUF", "HUB_VBUS_DET", at=(444.5, y2), lcsc=R_15K,
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
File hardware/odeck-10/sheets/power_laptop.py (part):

"""odeck-10 — laptop power sheet: LM51770 4-switch buck-boost (VIN 9-48 V -> VBB_OUT 5.1/9/15/20/28 V x 5 A),
voltage select by PMG1 GPIOs (VBB_VSEL0..2) through a slew-limited feedback network, LM74800 source switch
VBB_OUT -> VBUS_LAPTOP with hardware enable gating, LM74502 + TPS259470 bus-power sink switch
VBUS_LAPTOP -> +5V, independent latched ~30.8 V OVP (TLV3011), INA226 on laptop VBUS.
Design notes and calculations: docs/design/power_laptop.md"""
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    y = 66.04
    for i in range(4):
        s.c("4.7u/100V", "VIN", "GND", size="1210", at=(22.86 + i * 12.7, y), lcsc=C_4U7_100V)
    s.part("odeck:BSC0805LS", "Q", "BSC0805LS", at=(99.06, y), pins={"S": "BB_SW1", "G": "BB_G1", "D": "VIN", "EP": "VIN"},
           desc="100 V NFET, buck high side (HO1)")
    s.part("odeck:BSC0805LS", "Q", "BSC0805LS", at=(144.78, y), pins={"S": "GND", "G": "BB_G2", "D": "BB_SW1", "EP": "BB_SW1"},
           desc="100 V NFET, buck low side (LO1)")
    s.r("4m", "BB_SW1", "BB_LS", size="2512", at=(172.72, y), lcsc=R_SNS_4M, mpn="RLP25FEGR004",
        desc="Peak current sense 4 mOhm 1 % 2512 (CSA/CSB Kelvin)")
    s.part("odeck:XAL1010-103MED", "L", "10u", at=(190.5, y), pins={"1": "BB_LS", "2": "BB_SW2"},
           desc="10 uH 17.5 A shielded inductor")
    s.part("odeck:CSD18543Q3A", "Q", "CSD18543Q3A", at=(228.6, y), pins={"S": "GND", "G": "BB_G3", "D": "BB_SW2"},
           desc="60 V NFET, boost low side (LO2)")
    s.part("odeck:CSD18543Q3A", "Q", "CSD18543Q3A", at=(274.32, y), pins={"S": "BB_SW2", "G": "BB_G4", "D": "BB_PSO"},
           desc="60 V NFET, boost high side (HO2)")
    s.r("8m", "BB_PSO", "VBB_OUT", size="2512", at=(299.72, y), lcsc=R_SNS_8M, mpn="PE2512FKE070R008L",
        desc="Output current sense 8 mOhm 1 % 2512 (ISNSP/ISNSN Kelvin)")
    y = 99.06
    for i in range(4):
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        s.c("10u/50V", "VBB_OUT", "GND", size="1210", at=(137.16 + i * 10.16, y), lcsc=C_10U_50V)
    for i in range(2):
        s.part("Device:C_Polarized", "C", "100u/35V", "Capacitor_SMD:CP_Elec_6.3x7.7", at=(162.56 + i * 12.7, y),
               pins={"1": "VBB_OUT", "2": "GND"}, lcsc=C_100U_35V_POLY, desc="Polymer 100 uF 35 V, VBB_OUT bulk")
    s.c("100n/50V", "VBB_OUT", "GND", size="0603", at=(193.04, y), lcsc=C_100N_50V)
    s.flag("VBB_OUT", at=(205.74, y))
    # gate resistors (0 R, footprints for EMI tuning)
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           "CSA/CSB filter 10 R + 10 R + 100 pF (tau 2 ns << 88 ns min on-time / 10). nFLT = VBB_PG (10k to +3V3).",
           at=(264.16, 12.7))
    s.part("odeck:LM51770DCPR", "U", "LM51770", at=(342.9, 132.08),
           pins={"BIAS": "BB_BIAS", "VIN": "VIN", "EN/UVLO": "BB_EN", "IMONOUT": "BB_IMON", "nFLT": "VBB_PG",
                 "DTRK": "GND", "SYNC": "BB_VCC", "MODE": "BB_MODE", "CFG": "BB_CFG", "SLOPE": "BB_SLOPE",
                 "RT": "BB_RT", "SS/ATRK": "BB_SS", "AGND": "GND", "COMP": "BB_COMP", "FB": "BB_FB",
                 "VOUT": "VBB_OUT", "ISNSN": "VBB_OUT", "ISNSP": "BB_PSO", "SW2": "BB_SW2", "HB2": "BB_HB2",
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    _nfet(s, "BB_PGH", "VBB_PG", "GND", at=(x + 96.52, y + 58.42),
          desc="Holds VBB_PG low while disabled and for >= 5.4 ms after enable (nFLT high-Z in shutdown / soft start)")
    s.part("Device:D", "D", "1N4148W", "Diode_SMD:D_SOD-123", at=(x + 116.84, y + 58.42), lcsc=D_1N4148W,
           pins={"A": "BB_ENKILL", "K": "BB_PGH"}, desc="Fast set of the VBB_PG hold (converter disabled)")
    s.r("1M", "BB_PGH", "BB_ENKILL", at=(x + 132.08, y + 58.42), lcsc=R_1M, desc="VBB_PG hold release delay")
    s.c("4.7n", "BB_PGH", "GND", at=(x + 142.24, y + 58.42), lcsc=C_4N7, desc="tau 4.7 ms -> release 5.4-9.2 ms")
    x, y = 40.64, 292.1
    s.part("Device:D_Zener", "D", "BZT52C5V1", "Diode_SMD:D_SOD-123", at=(x, y), lcsc="C173407",
           pins={"K": "BB_ENKILL", "A": "GND"}, desc="5.1 V zener, gate clamp")
    s.r("470k", "VIN", "BB_ENKILL", size="0805", at=(x + 15.24, y), lcsc=R_470K_0805)
    _nfet(s, "BB_ENKILL", "BB_EN", "GND", at=(x + 45.72, y), desc="Pulls LM51770 EN/UVLO low (converter off)")
    _nfet(s, "VBB_EN", "BB_ENKILL", "BB_ENS", at=(x + 78.74, y), desc="Enable AND: VBB_EN")
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    _note(s, "4. LAPTOP SOURCE SWITCH  VBB_OUT -> VBUS_LSW -> 5 mOhm -> VBUS_LAPTOP\n"
           "LM74800-Q1: Q (DGATE) = ideal diode (blocks laptop -> VBB_OUT in < 1 us), Q (HGATE) = on/off,\n"
           "  common drain, 2x BSC026N08NS5 (80 V, 2.6 mOhm @10 V; same FET as power_input): 5 A -> 0.13 W total.\n"
           "HARDWARE ENABLE: SRC_ON = LAPTOP_SRC_EN AND EXT_PWR_PRESENT AND (VBB_PG AND LAPTOP_OVP_N AND PG5_DLY)\n"
           "  74LVC1G11 3-input AND; VBB_PG and LAPTOP_OVP_N (both open-drain, 10k pull-ups) diode-ANDed by BAT54A;\n"
           "  2 FETs pull SRC_PGOK low unless the delayed PG_5V (SNK_PGD) is high: the source can only close after the\n"
           "  bus-power sink has been released (same delayed PG_5V) and +5V runs from the LM5148.\n"
           "  100k pull-downs: unpowered logic or floating PMG1 GPIO -> switch OFF.\n"
           "INTERLOCK: SRC_ON also forces the sink switch off (Q on SNK_ON, us) while the source HGATE needs ms:\n"
           "  the sink is released by EXT_PWR_PRESENT AND PG5_DLY, the source needs both too -> never both on.\n"
           "Backstop OV on the LM74800 OV pin (independent of logic and +3V3): 255k/10k from VBUS_LAPTOP\n"
           "  via VSNS/SW -> HGATE off above 32.6 V (31.7-33.6 V).\n"
           "Soft turn-on: HGATE 55 uA into 22 nF -> 2.5 V/ms.",
           at=(406.4, 12.7))
    x, y = 421.64, 66.04
    s.part("odeck:BSC026N08NS5ATMA1", "Q", "BSC026N08NS5", at=(x, y), pins={"S": "VBB_OUT", "D": "SRC_MID", "G": "SRC_DGATE"},
           desc="80 V NFET, source ideal diode")
    s.part("odeck:BSC026N08NS5ATMA1", "Q", "BSC026N08NS5", at=(x + 50.8, y), pins={"S": "VBUS_LSW", "D": "SRC_MID", "G": "SRC_HGATE"},
           desc="80 V NFET, source on/off")
    s.part("odeck:LM74800QDRRRQ1", "U", "LM74800-Q1", at=(x + 25.4, y + 38.1),
           pins={"DGATE": "SRC_DGATE", "A": "VBB_OUT", "VSNS": "VBUS_LAPTOP", "SW": "SRC_OVT", "OV": "SRC_OV",
                 "EN/UVLO": "SRC_ON", "GND": "GND", "HGATE": "SRC_HGATE", "OUT": "VBUS_LSW", "VS": "SRC_MID",
                 "CAP": "SRC_CAP", "C": "SRC_MID"},
           nc=["RTN"], desc="Ideal diode + load switch controller, laptop source (RTN pad floating)")
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    # enable logic
    y3 = 165.1
    s.part("74xGxx:74LVC1G11", "U", "SN74LVC1G11", "Package_TO_SOT_SMD:SOT-23-6", at=(x2 + 22.86, y3), lcsc="C22046",
           pins={"1": "LAPTOP_SRC_EN", "3": "EXT_PWR_PRESENT", "6": "SRC_PGOK", "4": "SRC_ON", "5": "+3V3", "2": "GND"},
           desc="3-input AND, source enable")
    s.part("Diode:BAT54A", "D", "BAT54A", "Package_TO_SOT_SMD:SOT-23", at=(x2 + 91.44, y3), lcsc="C130910",
           pins={"3": "SRC_PGOK", "1": "VBB_PG", "2": "LAPTOP_OVP_N"}, desc="Diode AND (common anode)")
    s.r("10k", "SRC_PGOK", "+3V3", at=(x2 + 119.38, y3), lcsc=R_10K)
    s.r("100k", "LAPTOP_SRC_EN", "GND", at=(x2 + 129.54, y3), lcsc=R_100K)
    _nfet(s, "SNK_PGD", "SRC_PG5N", "GND", at=(x2 + 22.86, y3 + 22.86), desc="PG_5V (delayed) inverter")
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    s.r("5m", "VBUS_LSW", "VBUS_LAPTOP", size="1206", at=(x, y), lcsc=R_SNS_5M, mpn="RLM12FTCMR005",
        desc="INA226 shunt 5 mOhm 1 % 1206 1 W")
    s.part("odeck:INA226AIDGSR", "U", "INA226", at=(x + 40.64, y),
           pins={"VIN+": "VBUS_LSW", "VIN-": "VBUS_LAPTOP", "VBUS": "VBUS_LAPTOP", "VS+": "+3V3", "GND": "GND",
                 "A1": "+3V3", "A0": "GND", "SDA": "I2C_SYS_SDA", "SCL": "I2C_SYS_SCL"},
           nc=["Alert"], desc="Laptop VBUS current/voltage/power, I2C 0x44")
    s.c("100n", "+3V3", "GND", at=(x + 71.12, y), lcsc=C_100N)
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           "Stage 2, TPS259470A eFuse (28 V abs): true reverse-current blocking (+5V never back-feeds VBUS),\n"
           "  ILM 1.0k -> 3.34 A (3.0-3.7 A) active current limit, auto-retry; OVLO 40.2k/10k -> 6.0 V;\n"
           "  UVLO 121k/47k -> 4.3 V; dVdt 3.3 nF -> ~0.6 V/ms (soft start into the +5V bulk); ITIMER 1 nF.\n"
           "ENABLE: SNK_ON = LAPTOP_SNK_EN (10k / 47k) AND NOT (EXT_PWR_PRESENT AND PG5_DLY) AND NOT SRC_ON.\n"
           "  PG5_DLY = SNK_PGD = PG_5V (LM5148 PG, open drain, 100k to 5V_BUCK on power_rails) via 100k/100 nF,\n"
           "  rise delay 2.7-6.7 ms, fast fall through BAT46W: make-before-break hand-over, the sink stays on until\n"
           "  the buck regulates; overlap is safe (+5V OR: TPS259470A reverse blocking + LM74700 ideal diode).\n"
           "  LAPTOP_SNK_EN must be driven from a VBUS-powered domain in dead-battery (PMG1 VDDD from VBUS).\n"
           "Loss at 3 A: 9 x (8 m + 28 m + 5 m shunt) = 0.37 W.",
           at=(406.4, 279.4))
    x, y = 421.64, 337.82
    s.part("odeck:CSD18543Q3A", "Q", "CSD18543Q3A", at=(x, y), pins={"D": "VBUS_LSW", "S": "SNK_MID", "G": "SNK_GATE"},
           desc="60 V NFET, sink blocking switch")
    s.part("odeck:LM74502DDFR", "U", "LM74502", at=(x + 53.34, y),
           pins={"EN/UVLO": "SNK_ON", "GND": "GND", "VCAP": "SNK_VCAP", "VS": "VBUS_LSW", "GATE": "SNK_GATE",
                 "OV": "SNK_OV", "SRC": "SNK_MID"},
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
